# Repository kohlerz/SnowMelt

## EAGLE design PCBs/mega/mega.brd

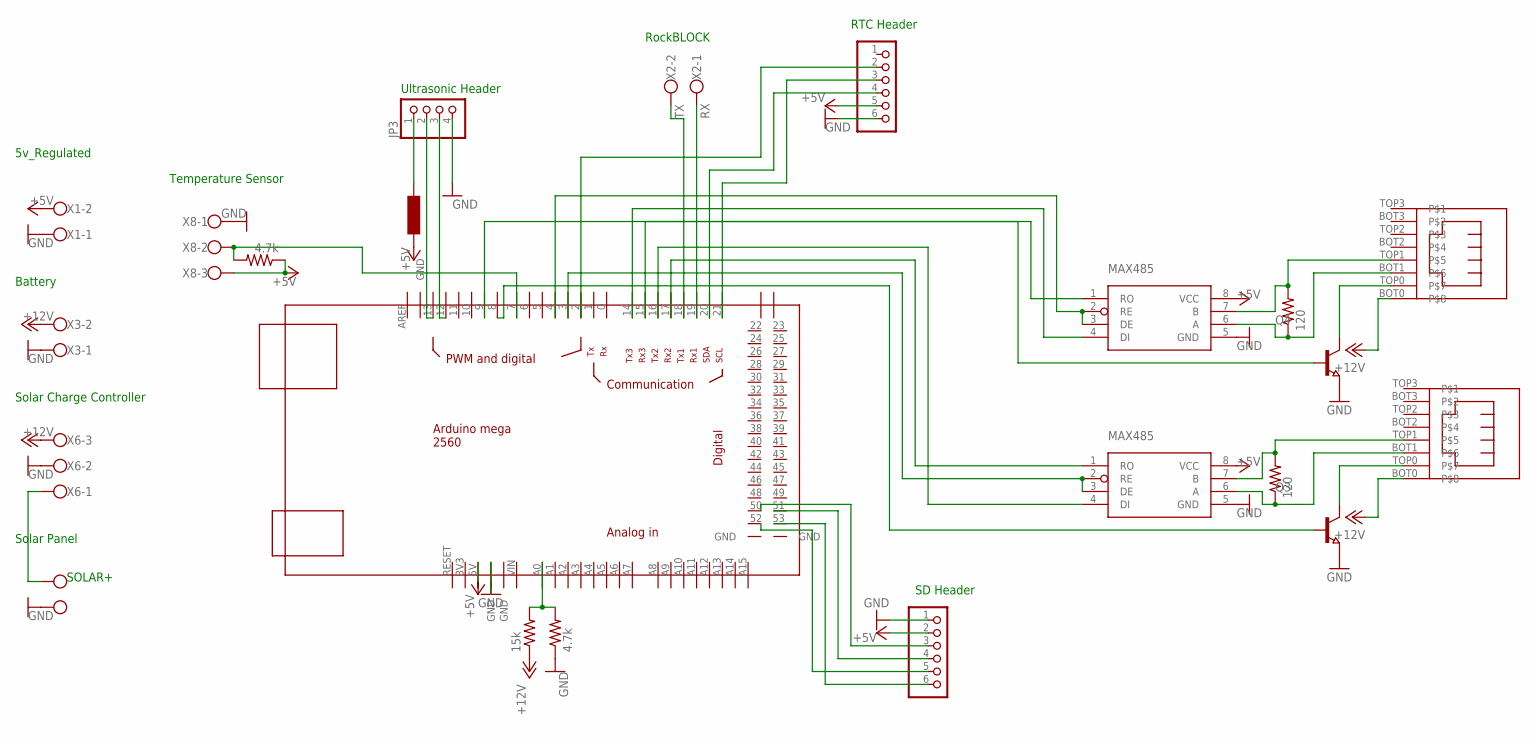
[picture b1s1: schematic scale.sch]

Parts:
JP1, JP2: PINHD-1X6; 1X06
JP3: PINHD-1X4; 1X04
JP4, JP5: ETHERNET
L1: 100uH; NLFV32T-101K-EF
Q3, Q4: NPN-TRANSISTOR_SOT23; SOT23
R1, R7: 120; R0805
R3, R9: 4.7k; R0805
R8: 15k; R0805
U$1, U$2: MAX485; SO08
U$3: MEGA_DEVICE; MEGAOUTLINE
X1, X2, X3, X7: W237-102
X6, X8: W237-103

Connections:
+5V: JP1.2, JP2.5, L1.P$1, R3.1, U$1.8 (VCC), U$2.8 (VCC), U$3.5V, X1.2, X8.3
+12V: JP4.BOT0, JP5.BOT0, R8.1, X3.2, X6.3
GND: JP1.1, JP2.6, JP3.4, Q3.2 (E), Q4.2 (E), R9.1, U$1.5 (GND), U$2.5 (GND), U$3.GND@2 (GND), X1.1, X3.1, X6.2, X7.1, X8.1
unnamed: JP4.TOP1, R1.2, U$1.7 (B)
unnamed: JP4.BOT1, R1.1, U$1.6 (A)
unnamed: JP5.TOP1, R7.2, U$2.7 (B)
unnamed: JP5.BOT1, R7.1, U$2.6 (A)
unnamed: U$2.1 (RO), U$3.17
unnamed: U$2.4 (DI), U$3.16
unnamed: U$1.1 (RO), U$3.15
unnamed: U$1.4 (DI), U$3.14
unnamed: JP2.2, U$3.2
unnamed: U$2.2 (RE), U$2.3 (DE), U$3.3
unnamed: U$1.2 (RE), U$1.3 (DE), U$3.4
unnamed: JP2.3, U$3.21
unnamed: JP2.4, U$3.20
unnamed: JP1.6, U$3.53
unnamed: JP1.5, U$3.52
unnamed: JP1.4, U$3.51
unnamed: JP1.3, U$3.50
unnamed: JP3.2, U$3.13
unnamed: JP3.3, U$3.12
unnamed: Q3.1 (B), U$3.8
unnamed: JP4.TOP0, Q4.3 (C)
unnamed: JP5.TOP0, Q3.3 (C)
unnamed: Q4.1 (B), U$3.9
unnamed: JP3.1, L1.P$2
unnamed: R8.2, R9.2, U$3.A0
unnamed: X6.1, X7.2
unnamed: R3.2, U$3.7, X8.2
RX: U$3.19, X2.1
TX: U$3.18, X2.2

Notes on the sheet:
SOLAR+
5v_Regulated
Battery
Solar Charge Controller
Solar Panel
RockBLOCK
Temperature Sensor
Ultrasonic Header
RTC Header
SD Header

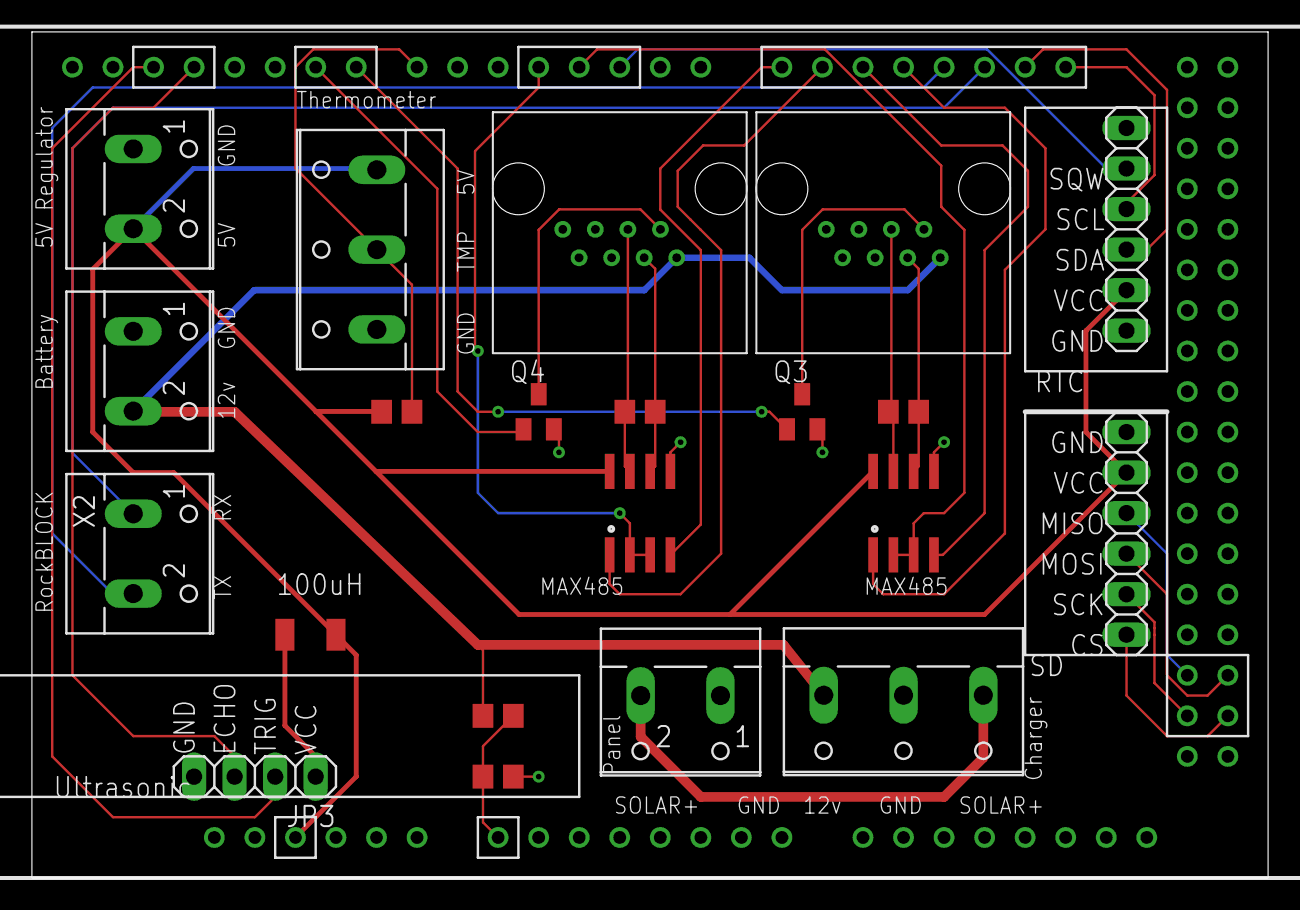
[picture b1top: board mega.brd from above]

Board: 2 copper layers, 77.5 x 53.0 mm, 22 parts (0 on the bottom side), 32 nets.

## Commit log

2021-08-06 Using ArduinoJson Library
2021-08-17 Upload Scale STL Files
2021-08-28 Embedded code on prototype
    This code runs on the first SNOTEL device
2021-11-07 Shrunk scales to fit inside bags
2021-11-07 Added scale top for easy prototyping
2021-11-12 Added PCB information and organized all the files
2022-11-27 Updated ESP email code
    Google changed gmail access tokens and I had to create an application code in order to send emails with the snowmelt2022 account
2022-11-27 Add WiFi Mega DIP Chart
